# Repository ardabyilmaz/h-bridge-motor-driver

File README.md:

# MOSFET H-Bridge Motor Driver

A discrete MOSFET based H-Bridge driver for DC motors.

## Features
- Motor voltage: 6V – 24V
- Current: up to 10A (depends on MOSFET)
- Simple design
- Logic level control

## Hardware
Components used:
- 2x P-channel MOSFET
- 2x N-channel MOSFET
- Gate resistors
- Pull-down/up resistors
- 4x6N137 High speed optocoupler

## Schematic
[Schematic PDF](Schematic.pdf)

## BOM
| Component | Value |
|-----------|------|
| MOSFET | IRLZ44N |
| MOSFET | IRF4905 |
| R1 | 10k |
| R2 | 100Ω |

## License
MIT License

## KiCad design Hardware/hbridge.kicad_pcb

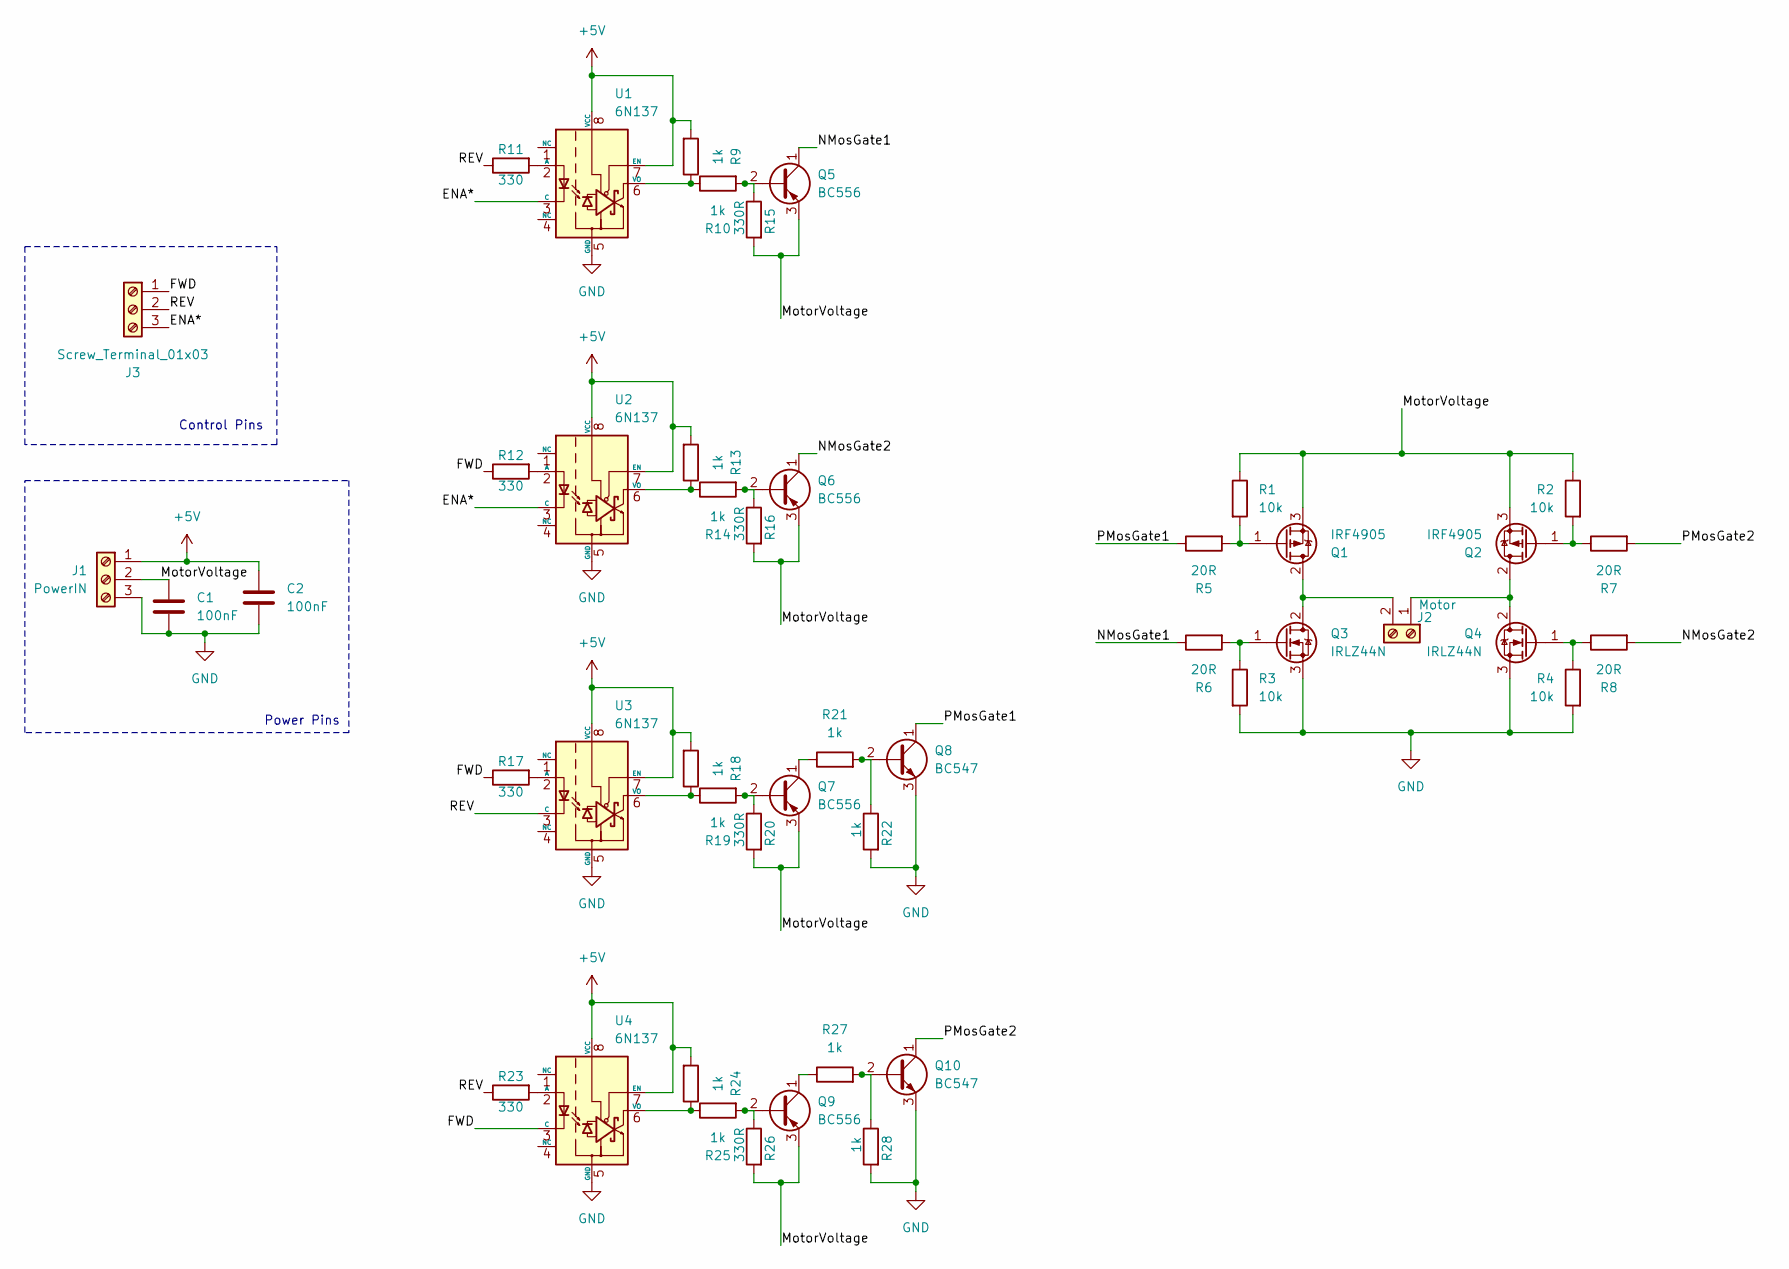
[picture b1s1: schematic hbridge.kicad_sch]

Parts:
C1, C2: 100nF; C_Disc_D5.0mm_W2.5mm_P5.00mm
J1: PowerIN; TerminalBlock_Phoenix_MKDS-3-3-5.08_1x03_P5.08mm_Horizontal
J2: Motor; TerminalBlock_Phoenix_MKDS-3-3-5.08_1x03_P5.08mm_Horizontal
J3: Screw_Terminal_01x03; TerminalBlock_Phoenix_MKDS-3-3-5.08_1x03_P5.08mm_Horizontal
Q1, Q2: IRF4905; TO-220-3_Vertical
Q3, Q4: IRLZ44N; TO-220-3_Vertical
Q5, Q6, Q7, Q9: BC556; TO-92_Inline
Q8, Q10: BC547; TO-92_Inline
R1, R2, R3, R4: 10k; R_Axial_DIN0204_L3.6mm_D1.6mm_P7.62mm_Horizontal
R5, R6, R7, R8: 20R; R_Axial_DIN0204_L3.6mm_D1.6mm_P7.62mm_Horizontal
R9, R10, R13, R14, R18, R19, R21, R22, R24, R25, R27, R28: 1k; R_Axial_DIN0204_L3.6mm_D1.6mm_P7.62mm_Horizontal
R11, R12, R17, R23: 330; R_Axial_DIN0204_L3.6mm_D1.6mm_P7.62mm_Horizontal
R15, R16, R20, R26: 330R; R_Axial_DIN0204_L3.6mm_D1.6mm_P7.62mm_Horizontal
U1, U2, U3, U4: 6N137; DIP-8_W7.62mm

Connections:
+5V: C2.1, J1.1, R9.2, R13.2, R18.2, R24.2, U1.7 (EN), U1.8 (VCC), U2.7 (EN), U2.8 (VCC), U3.7 (EN), U3.8 (VCC), U4.7 (EN), U4.8 (VCC)
/ENA*: J3.3, U1.3 (C), U2.3 (C)
/FWD: J3.1, R12.1, R17.1, U4.3 (C)
/MotorVoltage: C1.1, J1.2, Q1.3 (S), Q2.3 (S), Q5.3 (E), Q6.3 (E), Q7.3 (E), Q9.3 (E), R1.1, R2.1, R15.2, R16.2, R20.2, R26.2
/NMosGate1: Q5.1 (C), R6.1
/NMosGate2: Q6.1 (C), R8.2
/PMosGate1: Q8.1 (C), R5.1
/PMosGate2: Q10.1 (C), R7.2
/REV: J3.2, R11.1, R23.1, U3.3 (C)
GND: C1.2, C2.2, J1.3, Q3.3 (S), Q4.3 (S), Q8.3 (E), Q10.3 (E), R3.2, R4.2, R22.2, R28.2, U1.5 (GND), U2.5 (GND), U3.5 (GND), U4.5 (GND)
unnamed: J2.1, Q2.2 (D), Q4.2 (D)
unnamed: J2.2, Q1.2 (D), Q3.2 (D)
unnamed: Q1.1 (G), R1.2, R5.2
unnamed: Q2.1 (G), R2.2, R7.1
unnamed: Q3.1 (G), R3.1, R6.2
unnamed: Q4.1 (G), R4.1, R8.1
unnamed: Q5.2 (B), R10.2, R15.1
unnamed: Q6.2 (B), R14.2, R16.1
unnamed: Q7.2 (B), R19.2, R20.1
unnamed: Q7.1 (C), R21.1
unnamed: Q8.2 (B), R21.2, R22.1
unnamed: Q9.2 (B), R25.2, R26.1
unnamed: Q9.1 (C), R27.1
unnamed: Q10.2 (B), R27.2, R28.1
unnamed: R11.2, U1.2 (A)
unnamed: R9.1, R10.1, U1.6 (VO)
unnamed: R12.2, U2.2 (A)
unnamed: R13.1, R14.1, U2.6 (VO)
unnamed: R17.2, U3.2 (A)
unnamed: R18.1, R19.1, U3.6 (VO)
unnamed: R23.2, U4.2 (A)
unnamed: R24.1, R25.1, U4.6 (VO)

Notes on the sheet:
Power Pins
Control Pins

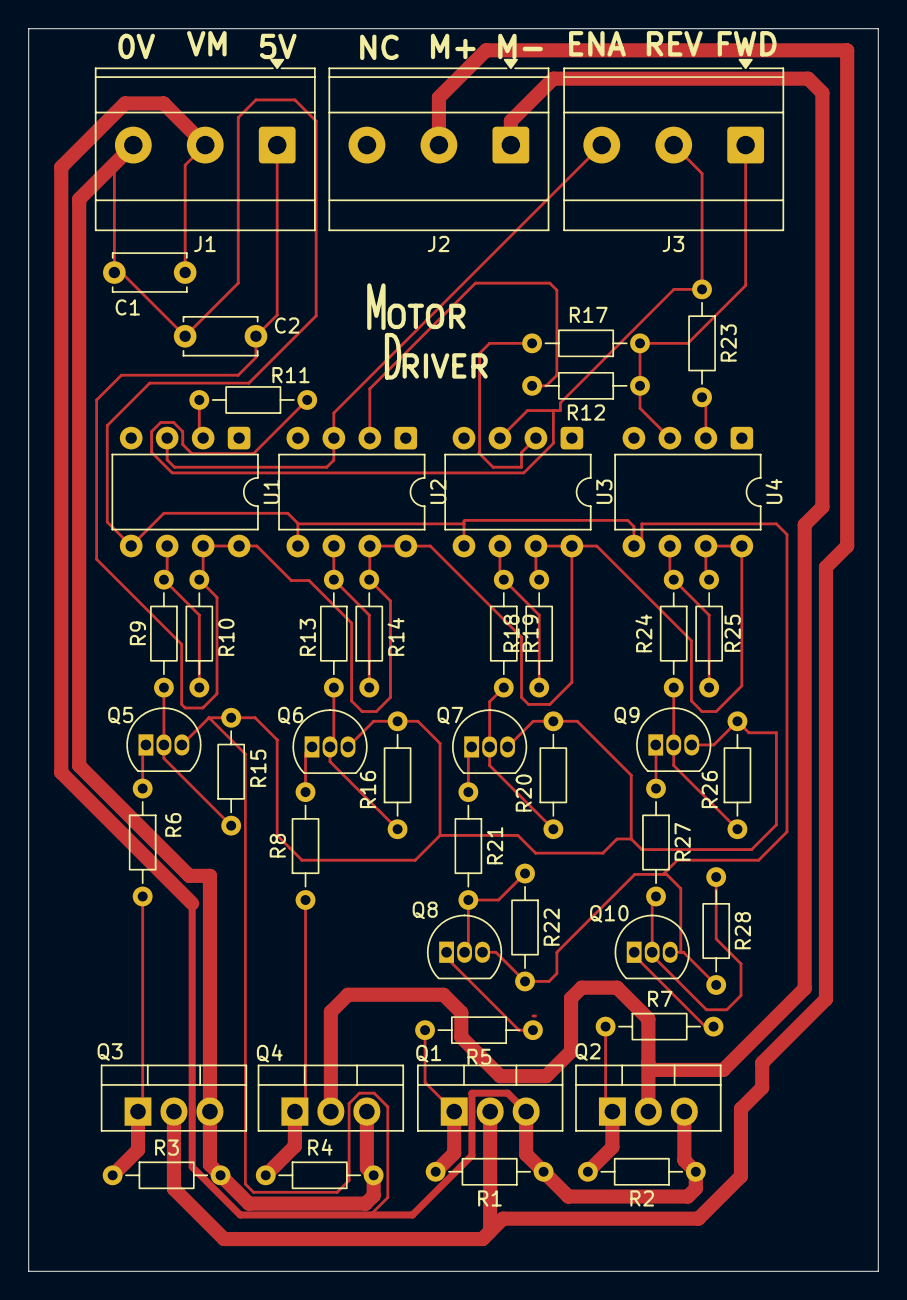
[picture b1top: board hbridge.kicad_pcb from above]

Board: 2 copper layers, 60.0 x 87.8 mm, 47 parts (0 on the bottom side), 32 nets.

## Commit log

2026-05-07 Create a
2026-05-07 Create c
2026-05-07 Moved Schematic.pdf
2026-05-07 moved
2026-05-07 Added kiCad files.
